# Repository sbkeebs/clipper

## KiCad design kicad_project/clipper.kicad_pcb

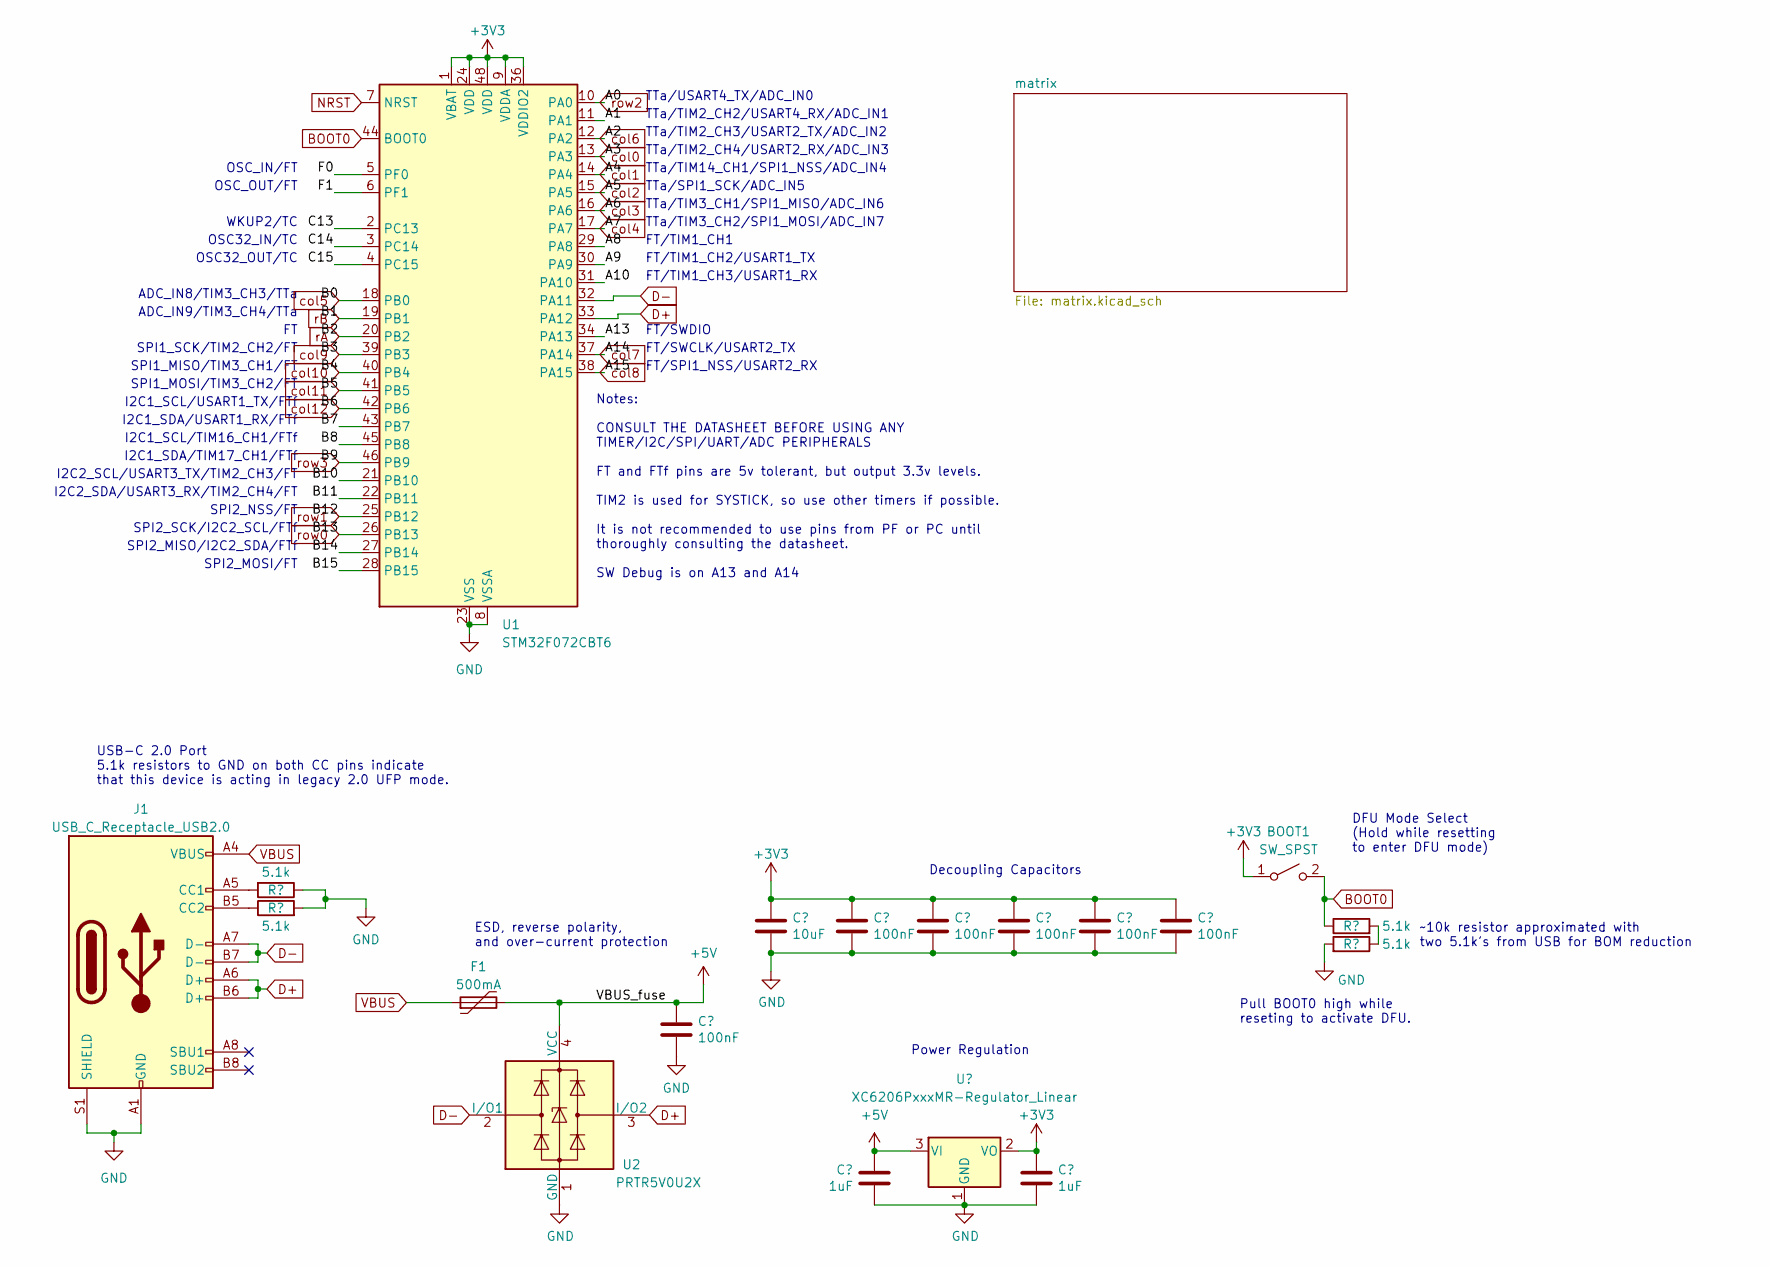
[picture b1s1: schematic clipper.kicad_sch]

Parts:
BOOT1: SW_SPST; SW_SPST_TL3342
C1: 10uF; C_0402_1005Metric; LCSC C307331
C2, C3, C4, C5, C6, C7: 100nF; C_0402_1005Metric; LCSC C307331
C8, C9: 1uF; C_0402_1005Metric; LCSC C307331
F1: 500mA; Fuse_1206_3216Metric; LCSC C135341
J1: USB_C_Receptacle_USB2.0; USB_C_Receptacle_HRO_TYPE-C-31-M-12; JlcRotOffset 180
R1, R2, R3, R4: 5.1k; R_0402_1005Metric
U1: STM32F072CBT6; LQFP-48_7x7mm_P0.5mm; JlcRotOffset 90
U2: PRTR5V0U2X; SOT-143; LCSC C2827688
U3: XC6206PxxxMR-Regulator_Linear; SOT-23; LCSC C5446

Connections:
+3V3: BOOT1.1 (A), C1.1, C2.1, C3.1, C4.1, C5.1, C6.1, C9.1, U1.1 (VBAT), U1.9 (VDDA), U1.24 (VDD), U1.36 (VDDIO2), U1.48 (VDD), U3.2 (VO)
+5V: C7.1, C8.1, F1.2, U2.4 (VCC), U3.3 (VI)
/A1: U1.11 (PA1)
/A8: U1.29 (PA8)
/A9: U1.30 (PA9)
/A10: U1.31 (PA10)
/A13: U1.34 (PA13)
/B7: U1.43 (PB7)
/B8: U1.45 (PB8)
/B10: U1.21 (PB10)
/B11: U1.22 (PB11)
/B14: U1.27 (PB14)
/B15: U1.28 (PB15)
/C13: U1.2 (PC13)
/C14: U1.3 (PC14)
/C15: U1.4 (PC15)
/F0: U1.5 (PF0)
/F1: U1.6 (PF1)
BOOT0: BOOT1.2 (B), R3.1, U1.44 (BOOT0)
D+: J1.A6 (D+), J1.B6 (D+), U1.33 (PA12), U2.3 (I/O2)
D-: J1.A7 (D-), J1.B7 (D-), U1.32 (PA11), U2.2 (I/O1)
GND: C1.2, C2.2, C3.2, C4.2, C5.2, C6.2, C7.2, C8.2, C9.2, J1.A1 (GND), J1.A12 (GND), J1.B1 (GND), J1.B12 (GND), J1.S1 (SHIELD), R1.1, R2.2, R4.2, U1.8 (VSSA), U1.23 (VSS), U1.35 (VSS), U1.47 (VSS), U2.1 (GND), U3.1 (GND); also elsewhere on the board
NRST: U1.7 (NRST)
unnamed: J1.A5 (CC1), R1.2
unnamed: J1.B5 (CC2), R2.1
unnamed: R3.2, R4.1
VBUS: F1.1, J1.A4 (VBUS), J1.A9 (VBUS), J1.B4 (VBUS), J1.B9 (VBUS)
col0: U1.13 (PA3); also elsewhere on the board
col1: U1.14 (PA4); also elsewhere on the board
col2: U1.15 (PA5); also elsewhere on the board
col3: U1.16 (PA6); also elsewhere on the board
col4: U1.17 (PA7); also elsewhere on the board
col5: U1.18 (PB0); also elsewhere on the board
col6: U1.12 (PA2); also elsewhere on the board
col7: U1.37 (PA14); also elsewhere on the board
col8: U1.38 (PA15); also elsewhere on the board
col9: U1.39 (PB3); also elsewhere on the board
col10: U1.40 (PB4); also elsewhere on the board
col11: U1.41 (PB5); also elsewhere on the board
col12: U1.42 (PB6); also elsewhere on the board
rA: U1.20 (PB2); also elsewhere on the board
rB: U1.19 (PB1); also elsewhere on the board
row0: U1.26 (PB13); also elsewhere on the board
row1: U1.25 (PB12); also elsewhere on the board
row2: U1.10 (PA0); also elsewhere on the board
row3: U1.46 (PB9); also elsewhere on the board

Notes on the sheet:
SPI1_SCK/TIM2_CH2/FT
FT/TIM1_CH1
FT/TIM1_CH3/USART1_RX
SPI2_NSS/FT
Notes: CONSULT THE DATASHEET BEFORE USING ANY TIMER/I2C/SPI/UART/ADC PERIPHERALS FT and FTf pins are 5v tolerant, but output 3.3v levels. TIM2 is used for SYSTICK, so use other timers if possible. It is not recommended to use pins from PF or PC until thoroughly consulting the datasheet. SW Debug is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
TTa/TIM2_CH4/USART2_RX/ADC_IN3
FT/SWDIO
Decoupling Capacitors
SPI1_MOSI/TIM3_CH2/FT
ADC_IN9/TIM3_CH4/TTa
I2C2_SCL/USART3_TX/TIM2_CH3/FT
SPI2_MISO/I2C2_SDA/FTf
FT/SWCLK/USART2_TX
I2C1_SCL/TIM16_CH1/FTf
~10k resistor approximated with two 5.1k's from USB for BOM reduction
TTa/TIM2_CH2/USART4_RX/ADC_IN1
USB-C 2.0 Port 5.1k resistors to GND on both CC pins indicate that this device is acting in legacy 2.0 UFP mode.
TTa/TIM2_CH3/USART2_TX/ADC_IN2
OSC_IN/FT
DFU Mode Select (Hold while resetting to enter DFU mode)
WKUP2/TC
I2C2_SDA/USART3_RX/TIM2_CH4/FT
ADC_IN8/TIM3_CH3/TTa
Pull BOOT0 high while reseting to activate DFU.
I2C1_SDA/TIM17_CH1/FTf
TTa/SPI1_SCK/ADC_IN5
TTa/TIM3_CH1/SPI1_MISO/ADC_IN6
TTa/TIM3_CH2/SPI1_MOSI/ADC_IN7
OSC32_OUT/TC
FT/SPI1_NSS/USART2_RX
SPI1_MISO/TIM3_CH1/FT
OSC32_IN/TC
TTa/TIM14_CH1/SPI1_NSS/ADC_IN4
I2C1_SDA/USART1_RX/FTf
SPI2_MOSI/FT
FT/TIM1_CH2/USART1_TX
Power Regulation
SPI2_SCK/I2C2_SCL/FTf
OSC_OUT/FT
ESD, reverse polarity, and over-current protection

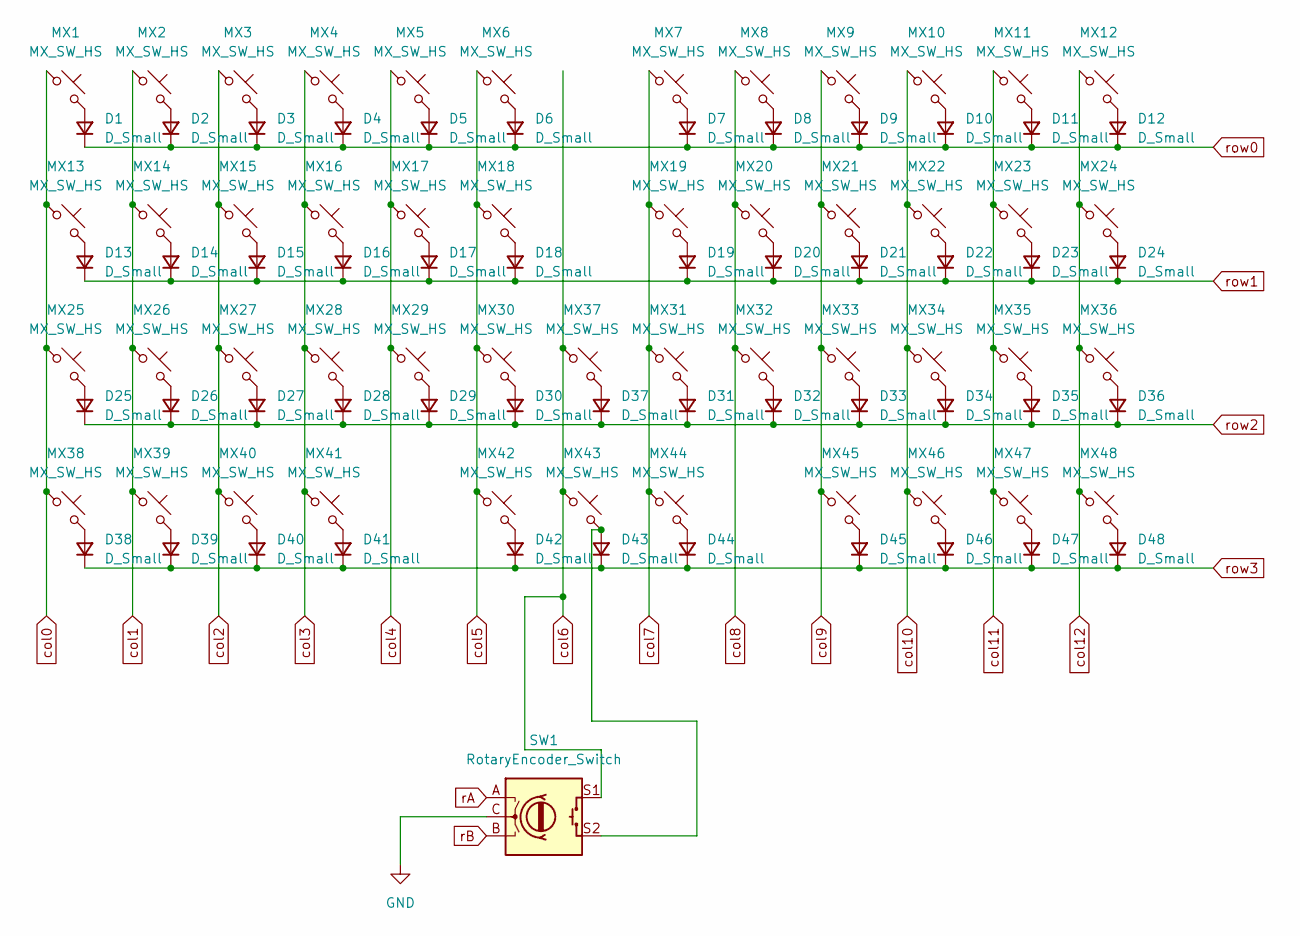
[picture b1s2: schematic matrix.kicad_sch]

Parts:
D1, D2, D3, D4, D5, D6, D7, D8, D9, D10, D11, D12, D13, D14, D15, D16, D17, D18, D19, D20, D21, D22, D23, D24, D25, D26, D27, D28, D29, D30, D31, D32, D33, D34, D35, D36, D37, D38, D39, D40, D41, D42, D43, D44, D45, D46, D47, D48: D_Small; D_SOD-323
MX1, MX12: MX_SW_HS; SW_MX_HS_CPG151101S11_1.5u
MX2, MX3, MX4, MX5, MX6, MX7, MX8, MX9, MX10, MX11, MX14, MX15, MX16, MX17, MX18, MX19, MX20, MX21, MX22, MX23, MX25, MX26, MX27, MX28, MX29, MX30, MX31, MX32, MX33, MX34, MX35, MX36, MX37, MX38, MX39, MX40, MX41, MX42, MX43, MX44, MX45, MX46, MX47, MX48: MX_SW_HS; SW_MX_HS_CPG151101S11_1u
MX13, MX24: MX_SW_HS; SW_MX_HS_CPG151101S11_1.25u
SW1: RotaryEncoder_Switch; ROT_Alps_EC11E-Switch

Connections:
GND: SW1.C; also elsewhere on the board
unnamed: D1.2 (A), MX1.2
unnamed: D2.2 (A), MX2.2
unnamed: D3.2 (A), MX3.2
unnamed: D4.2 (A), MX4.2
unnamed: D5.2 (A), MX5.2
unnamed: D6.2 (A), MX6.2
unnamed: D7.2 (A), MX7.2
unnamed: D8.2 (A), MX8.2
unnamed: D9.2 (A), MX9.2
unnamed: D10.2 (A), MX10.2
unnamed: D11.2 (A), MX11.2
unnamed: D12.2 (A), MX12.2
unnamed: D13.2 (A), MX13.2
unnamed: D14.2 (A), MX14.2
unnamed: D15.2 (A), MX15.2
unnamed: D16.2 (A), MX16.2
unnamed: D17.2 (A), MX17.2
unnamed: D18.2 (A), MX18.2
unnamed: D19.2 (A), MX19.2
unnamed: D20.2 (A), MX20.2
unnamed: D21.2 (A), MX21.2
unnamed: D22.2 (A), MX22.2
unnamed: D23.2 (A), MX23.2
unnamed: D24.2 (A), MX24.2
unnamed: D25.2 (A), MX25.2
unnamed: D26.2 (A), MX26.2
unnamed: D27.2 (A), MX27.2
unnamed: D28.2 (A), MX28.2
unnamed: D29.2 (A), MX29.2
unnamed: D30.2 (A), MX30.2
unnamed: D31.2 (A), MX31.2
unnamed: D32.2 (A), MX32.2
unnamed: D33.2 (A), MX33.2
unnamed: D34.2 (A), MX34.2
unnamed: D35.2 (A), MX35.2
unnamed: D36.2 (A), MX36.2
unnamed: D37.2 (A), MX37.2
unnamed: D38.2 (A), MX38.2
unnamed: D39.2 (A), MX39.2
unnamed: D40.2 (A), MX40.2
unnamed: D41.2 (A), MX41.2
unnamed: D42.2 (A), MX42.2
unnamed: D43.2 (A), MX43.2, SW1.S2
unnamed: D44.2 (A), MX44.2
unnamed: D45.2 (A), MX45.2
unnamed: D46.2 (A), MX46.2
unnamed: D47.2 (A), MX47.2
unnamed: D48.2 (A), MX48.2
col0: MX1.1, MX13.1, MX25.1, MX38.1; also elsewhere on the board
col1: MX2.1, MX14.1, MX26.1, MX39.1; also elsewhere on the board
col2: MX3.1, MX15.1, MX27.1, MX40.1; also elsewhere on the board
col3: MX4.1, MX16.1, MX28.1, MX41.1; also elsewhere on the board
col4: MX5.1, MX17.1, MX29.1; also elsewhere on the board
col5: MX6.1, MX18.1, MX30.1, MX42.1; also elsewhere on the board
col6: MX37.1, MX43.1, SW1.S1; also elsewhere on the board
col7: MX7.1, MX19.1, MX31.1, MX44.1; also elsewhere on the board
col8: MX8.1, MX20.1, MX32.1; also elsewhere on the board
col9: MX9.1, MX21.1, MX33.1, MX45.1; also elsewhere on the board
col10: MX10.1, MX22.1, MX34.1, MX46.1; also elsewhere on the board
col11: MX11.1, MX23.1, MX35.1, MX47.1; also elsewhere on the board
col12: MX12.1, MX24.1, MX36.1, MX48.1; also elsewhere on the board
rA: SW1.A; also elsewhere on the board
rB: SW1.B; also elsewhere on the board
row0: D1.1 (K), D2.1 (K), D3.1 (K), D4.1 (K), D5.1 (K), D6.1 (K), D7.1 (K), D8.1 (K), D9.1 (K), D10.1 (K), D11.1 (K), D12.1 (K); also elsewhere on the board
row1: D13.1 (K), D14.1 (K), D15.1 (K), D16.1 (K), D17.1 (K), D18.1 (K), D19.1 (K), D20.1 (K), D21.1 (K), D22.1 (K), D23.1 (K), D24.1 (K); also elsewhere on the board
row2: D25.1 (K), D26.1 (K), D27.1 (K), D28.1 (K), D29.1 (K), D30.1 (K), D31.1 (K), D32.1 (K), D33.1 (K), D34.1 (K), D35.1 (K), D36.1 (K), D37.1 (K); also elsewhere on the board
row3: D38.1 (K), D39.1 (K), D40.1 (K), D41.1 (K), D42.1 (K), D43.1 (K), D44.1 (K), D45.1 (K), D46.1 (K), D47.1 (K), D48.1 (K); also elsewhere on the board

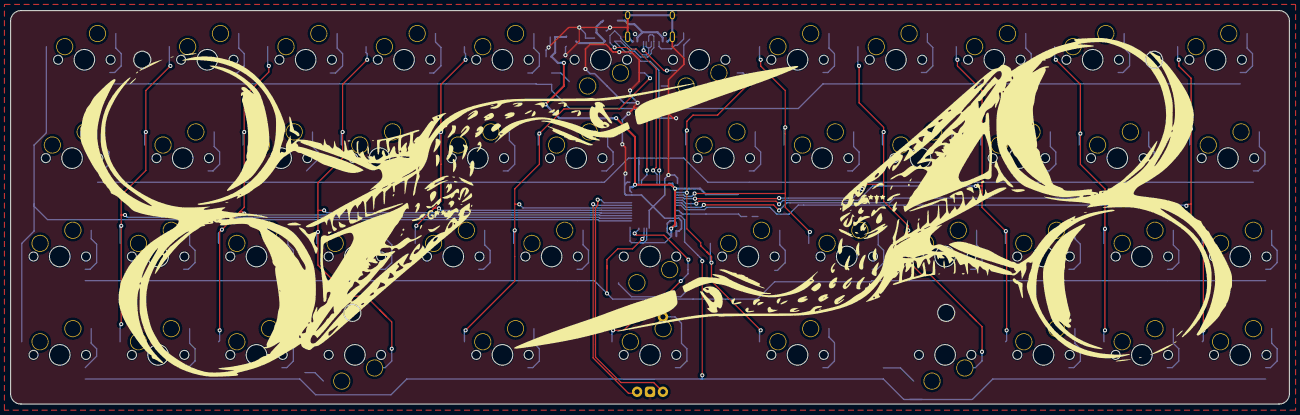
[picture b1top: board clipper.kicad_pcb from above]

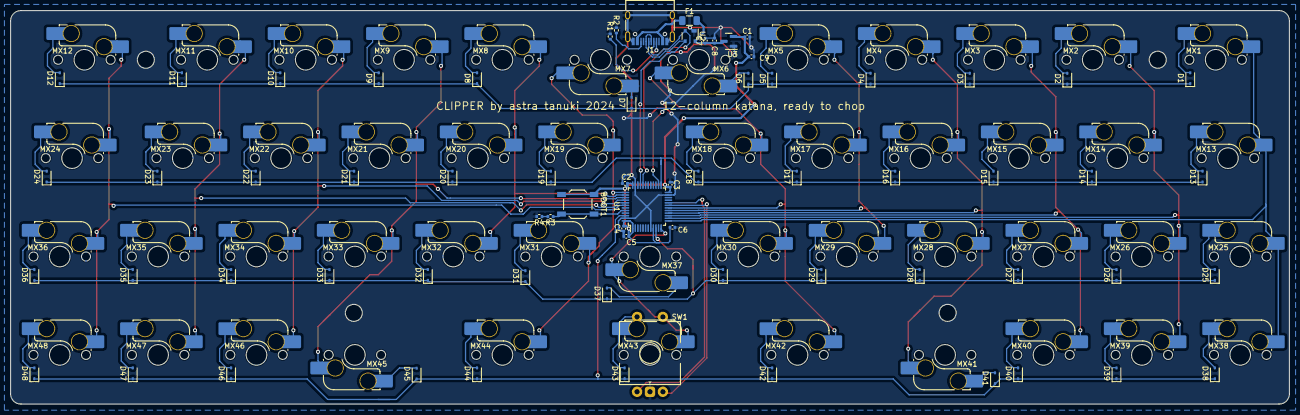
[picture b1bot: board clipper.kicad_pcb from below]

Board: 2 copper layers, 247.6 x 76.2 mm, 116 parts (116 on the bottom side), 77 nets.

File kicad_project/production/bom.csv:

Designator,Footprint,Quantity,Value,LCSC Part #
BOOT1,SW_SPST_TL3342,1,SW_SPST,C318884
C1,0402,1,10uF,C76991
"C2, C3, C4, C5, C6, C7",0402,6,100nF,C1525
"C8, C9",0402,2,1uF,C52923
"D1, D10, D11, D12, D13, D14, D15, D16, D17, D18, D19, D2, D20, D21, D22, D23, D24, D25, D26, D27, D28, D29, D3, D30, D31, D32, D33, D34, D35, D36, D37, D38, D39, D4, D40, D41, D42, D43, D44, D45, D46, D47, D48, D5, D6, D7, D8, D9",D_SOD-323,48,D_Small,C908234
F1,1206,1,500mA,C70068
J1,USB_C_Receptacle_HRO_TYPE-C-31-M-12,1,USB_C_Receptacle_USB2.0,C165948
"R1, R2, R3, R4",0402,4,5.1k,C144745
U1,LQFP-48_7x7mm_P0.5mm,1,STM32F072CBT6,C81720
U2,SOT-143,1,PRTR5V0U2X,C2827688
U3,SOT-23,1,XC6206PxxxMR-Regulator_Linear,C5446

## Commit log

2025-01-09 add firmware
2025-01-09 add case files
2025-01-09 add kicad files
2025-01-09 remove unneeded files
2025-01-13 add boop version
2025-01-13 add clipper plate for smaller print beds
2025-01-26 upload updated plate files
2025-01-26 plate readme
2025-01-26 fix typo
